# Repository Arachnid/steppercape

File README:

Schematics and firmware for the Beaglebone stepper cape.

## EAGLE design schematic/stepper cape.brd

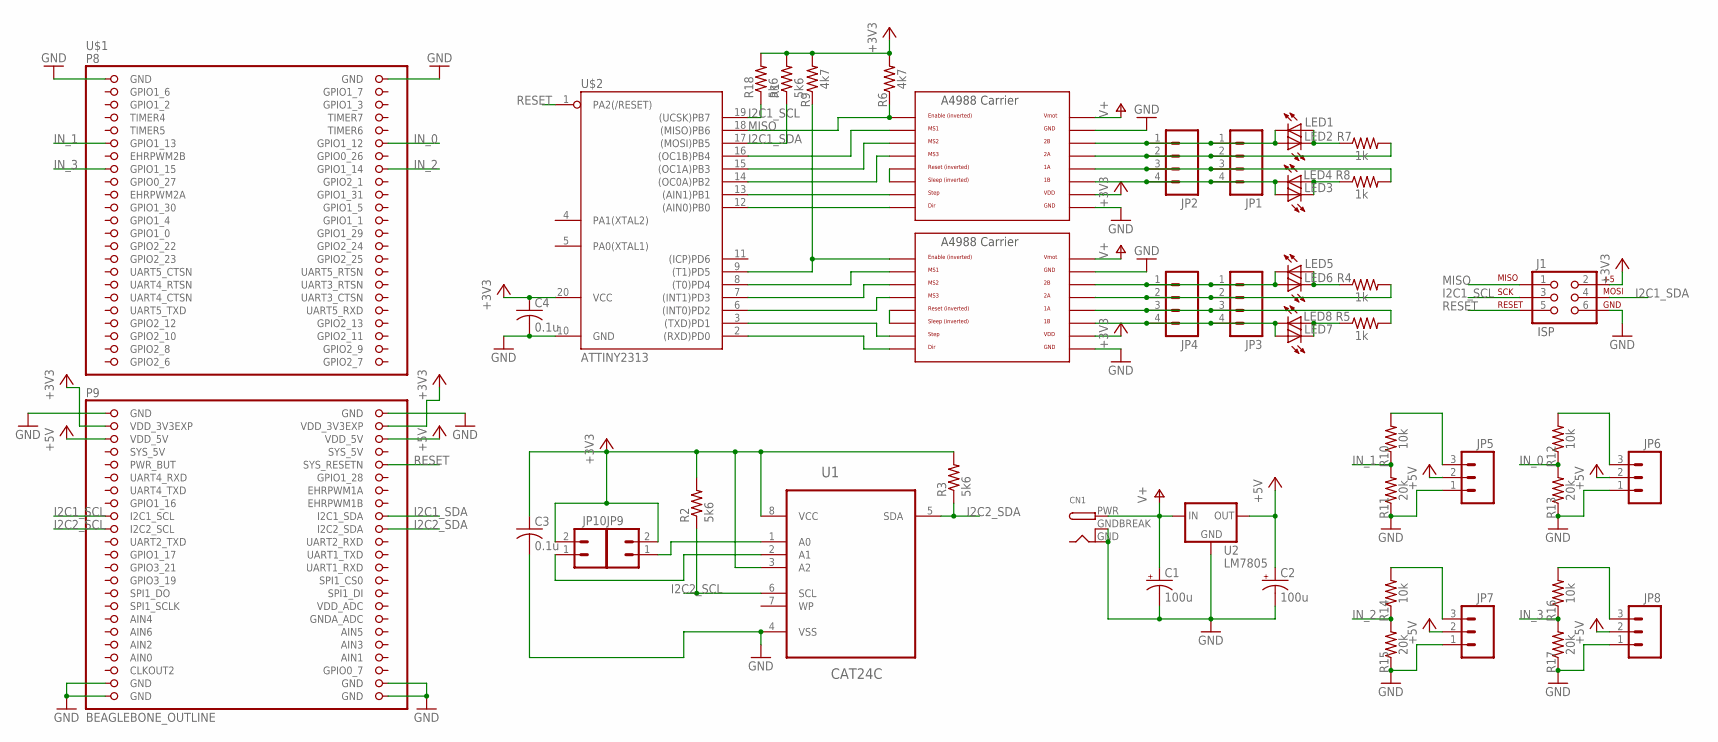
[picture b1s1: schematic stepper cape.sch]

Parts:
C1, C2: 100u; E2,5-6
C3, C4: 0.1u; C1206
CN1: DCBARRELPTH; DCJACK_2MM_PTH
J1: ISP; 2X3
JP1, JP3: M04SCREW; SCREWTERMINAL-3.5MM-4
JP2, JP4: M04PTH; 1X04
JP5, JP6, JP7, JP8: M03PTH; 1X03
JP9, JP10: M02PTH; 1X02
LED1, LED2, LED3, LED4, LED5, LED6, LED7, LED8: LEDCHIPLED_1206; CHIPLED_1206
R1, R2, R3, R18: 5k6; R1206
R4, R5, R7, R8: 1k; R1206
R6, R9: 4k7; R1206
R10, R12, R14, R16: 10k; R1206
R11, R13, R15, R17: 20k; R1206
U1: CAT24C; SOIC127P600X175-8N
U2: LM7805; TO220-IGO
U$1: BEAGLEBONE_OUTLINE; BEAGLEBONE_SHIELD
U$2: ATTINY2313; SO20L$
X, X1: A4988BREAKOUT

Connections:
+3V3: C3.1, C4.1, J1.2, JP9.2, JP10.2, R1.2, R2.2, R3.2, R6.2, R9.2, R18.2, U1.3 (A2), U1.8 (VCC), U$1.49 (VDD_3V3EXP), U$1.50 (VDD_3V3EXP), U$2.20 (VCC), X.VDD, X1.VDD
+5V: C2.+, JP5.2, JP6.2, JP7.2, JP8.2, U2.OUT, U$1.51 (VDD_5V), U$1.52 (VDD_5V)
AIN0: U$1.85 (AIN0)
AIN3: U$1.84 (AIN3)
GND: C1.-, C2.-, C3.2, C4.2, CN1.GND, CN1.GNDBREAK, J1.6, JP5.1, JP6.1, JP7.1, JP8.1, R11.1, R13.1, R15.1, R17.1, U1.4 (VSS), U2.GND, U$1.1 (GND), U$1.2 (GND), U$1.47 (GND), U$1.48 (GND), U$1.89 (GND), U$1.90 (GND), U$1.91 (GND), U$1.92 (GND), U$2.10 (GND), X.GND, X.GND@0 (GND), X1.GND, X1.GND@0 (GND)
GPIO1_6: U$1.3 (GPIO1_6)
GPIO1_7: U$1.4 (GPIO1_7)
GPIO2_6: U$1.45 (GPIO2_6)
GPIO2_7: U$1.46 (GPIO2_7)
GPIO2_8: U$1.43 (GPIO2_8)
GPIO2_9: U$1.44 (GPIO2_9)
GPIO2_11: U$1.42 (GPIO2_11)
I2C1_SCL: J1.3, R18.1, U$1.63 (I2C1_SCL), U$2.19 ((UCSK)PB7)
I2C1_SDA: J1.4, R1.1, U$1.64 (I2C1_SDA), U$2.17 ((MOSI)PB5)
I2C2_SCL: R2.1, U1.6 (SCL), U$1.65 (I2C2_SCL)
I2C2_SDA: R3.1, U1.5 (SDA), U$1.66 (I2C2_SDA)
IN_0: R12.1, R13.2, U$1.12 (GPIO1_12)
IN_1: R10.1, R11.2, U$1.11 (GPIO1_13)
IN_2: R14.1, R15.2, U$1.16 (GPIO1_14)
IN_3: R16.1, R17.2, U$1.15 (GPIO1_15)
MISO: J1.1, R6.1, U$2.18 ((MISO)PB6), X.EN
unnamed: JP9.1, U1.1 (A0)
unnamed: U$2.2 ((RXD)PD0), X1.DIR
unnamed: JP10.1, U1.2 (A1)
unnamed: U$2.3 ((TXD)PD1), X1.STEP
unnamed: JP1.1, JP2.1, LED1.C, LED2.A, X.2B
unnamed: U$2.6 ((INT0)PD2), X1.MS3
unnamed: U$2.7 ((INT1)PD3), X1.MS2
unnamed: U$2.8 ((T0)PD4), X1.MS1
unnamed: X1.RST, X1.SLP (SLEEP)
unnamed: JP3.1, JP4.1, LED5.C, LED6.A, X1.2B
unnamed: JP3.2, JP4.2, R4.2, X1.2A
unnamed: X.RST, X.SLP (SLEEP)
unnamed: JP1.2, JP2.2, R7.2, X.2A
unnamed: JP1.3, JP2.3, R8.2, X.1A
unnamed: JP1.4, JP2.4, LED3.A, LED4.C, X.1B
unnamed: LED1.A, LED2.C, R7.1
unnamed: JP3.3, JP4.3, R5.2, X1.1A
unnamed: LED3.C, LED4.A, R8.1
unnamed: JP3.4, JP4.4, LED7.A, LED8.C, X1.1B
unnamed: LED5.A, LED6.C, R4.1
unnamed: LED7.C, LED8.A, R5.1
unnamed: R9.1, U$2.9 ((T1)PD5), X1.EN
unnamed: U$2.12 ((AIN0)PB0), X.DIR
unnamed: U$2.13 ((AIN1)PB1), X.STEP
unnamed: JP6.3, R12.2
unnamed: JP5.3, R10.2
unnamed: JP7.3, R14.2
unnamed: JP8.3, R16.2
unnamed: U$2.14 ((OC0A)PB2), X.MS3
unnamed: U$2.15 ((OC1A)PB3), X.MS2
unnamed: U$2.16 ((OC1B)PB4), X.MS1
RESET: J1.5, U$1.56 (SYS_RESETN), U$2.1 (PA2(/RESET))
V+: C1.+, CN1.PWR, U2.IN, X.VMOT, X1.VMOT

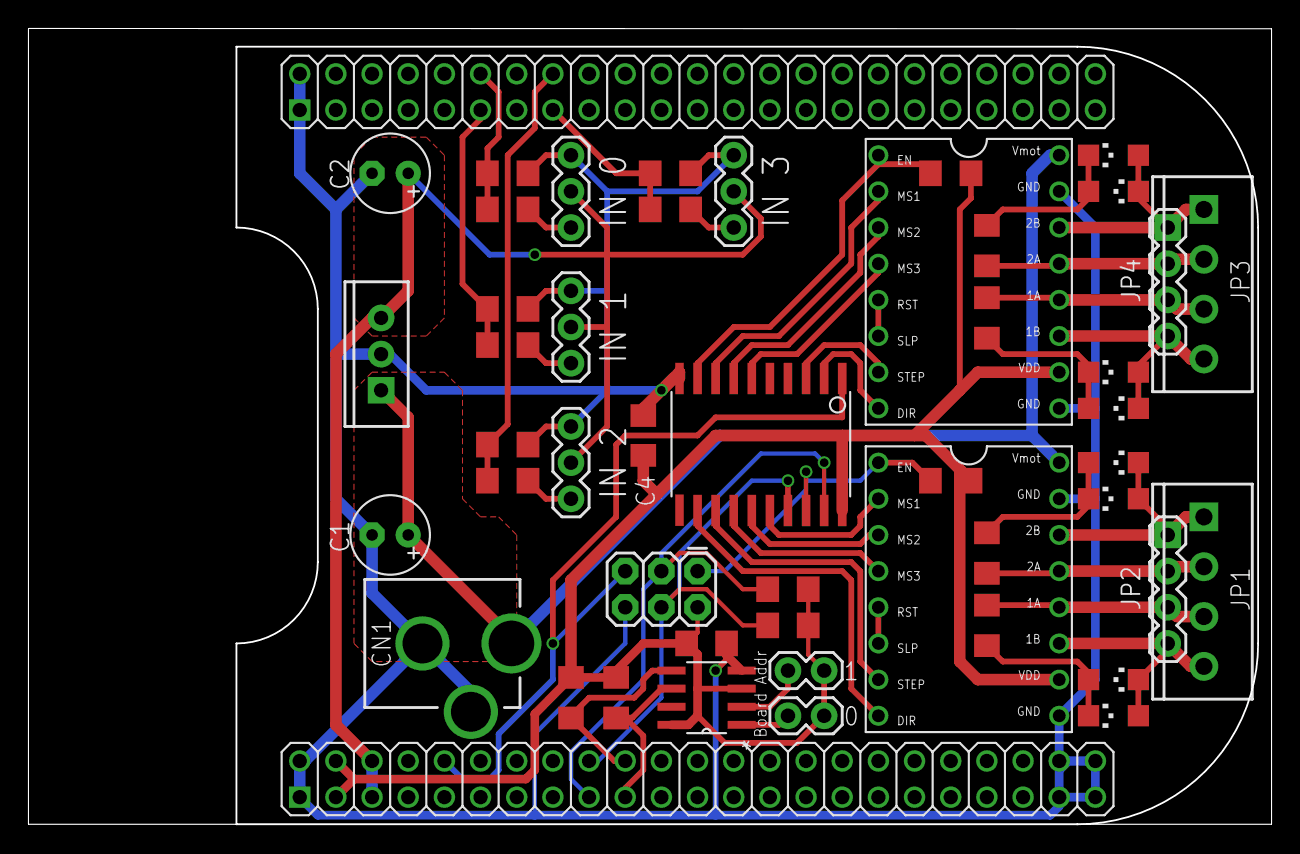
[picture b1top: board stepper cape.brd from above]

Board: 2 copper layers, 87.2 x 55.8 mm, 49 parts (1 on the bottom side), 45 nets.

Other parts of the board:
U$3: OSHW_FILLX500_NOTEXT

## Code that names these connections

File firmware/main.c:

/*
 * Stepper Cape - an I2C based stepper driver cape for the Beaglebone
 * Copyright (C) 2012 Nick Johnson
 *
 * This program is free software; you can redistribute it and/or
 * modify it under the terms of the GNU General Public License
 * as published by the Free Software Foundation; either version 2
 * of the License, or (at your option) any later version.
 * 
 * This program is distributed in the hope that it will be useful,
 * but WITHOUT ANY WARRANTY; without even the implied warranty of
 * MERCHANTABILITY or FITNESS FOR A PARTICULAR PURPOSE.  See the
 * GNU General Public License for more details.
 * 
 * You should have received a copy of the GNU General Public License
 * along with this program; if not, write to the Free Software
 * Foundation, Inc., 51 Franklin Street, Fifth Floor, Boston, MA  02110-1301, USA.
 */

#define F_CPU 8000000UL  // 8 MHz

#include <util/delay.h>
#include <avr/io.h>
#include <avr/eeprom.h>
#include <avr/interrupt.h>
#include <avr/pgmspace.h>
#include "register.h"
#include "usiTwiSlave.h"

FUSES = {
	.low = FUSE_SUT0 & FUSE_CKSEL3 & FUSE_CKSEL1 & FUSE_CKSEL0,
	.high = FUSE_SPIEN,
};

#define TRUE 1
#define FALSE 0

#define DDR_STEPPER0 DDRB
#define PORT_STEPPER0 PORTB
#define STEPPER0_DIR PB0
#define STEPPER0_EN PB6
#define STEPPER0_STEP PB1
#define STEPPER0_MS0 PB2
#define STEPPER0_MICROSTEP_MASK ((uint8_t)~(_BV(PB4) | _BV(PB3) | _BV(PB2)))

#define DDR_STEPPER1 DDRD
#define PORT_STEPPER1 PORTD
#define STEPPER1_DIR PD0
#define STEPPER1_EN PD5
#define STEPPER1_STEP PD1
#define STEPPER1_MS0 PD2
#define STEPPER1_MICROSTEP_MASK ((uint8_t)~(_BV(PD4) | _BV(PD3) | _BV(PD2)))

#define PORT_INPUTS PORTA
#define INPUT0 PA0
#define INPUT1 PA1

#define ENABLE_PWM_SETUP() (TCCR1A = 0, TCCR1B = _BV(WGM13) | _BV(WGM12), TIMSK |= _BV(ICIE1))

typedef uint8_t (*register_write_handler)(uint8_t reg, uint8_t oldval);

// Predefinitions of read/write handlers so we can reference them
uint8_t i2c_read(uint8_t reg, volatile uint8_t *value);
uint8_t i2c_write(uint8_t reg, uint8_t value);
void main(void) __attribute__((noreturn));

#define copy_bit(from_reg, from_bit, to_reg, to_bit) if((from_reg) & _BV(from_bit)) { \
    to_reg |= _BV(to_bit); \
} else { \
    to_reg &= ~_BV(to_bit); \
}

register_t registers;

#define BUFFER_CAPACITY 32
volatile uint8_t buffer[BUFFER_CAPACITY];
volatile uint8_t buffer_head = 0; // Oldest valid element
volatile uint8_t buffer_tail = 0; // First empty slot
volatile uint8_t buffer_nybble = 0;

// EEPROM copy of registers; updated on write to register 127.
register_t EEMEM eeprom_registers = {
    .reg = {
        .slave_addr = 0x26,
        .clk_flags = {
			.stall_stop = 0,
			.cs = 0,
		},
        .step_interval = 0,
        .limit_flags = {
			.s0_stop = 0,
			.s1_stop = 0,
			.i0_invert = 0,
			.i1_invert = 0,
		},
        .microstep = {
			.stepper0 = 0,
			.stepper1 = 0,
		},
        .buffer_free = BUFFER_CAPACITY,
        .buffer_append = 0
    }
};

volatile uint8_t eeprom_dirty = FALSE;

uint8_t write_noop(uint8_t reg, uint8_t oldval) {
	return TRUE;
}

uint8_t write_ignore(uint8_t reg, uint8_t oldval) {
	registers.bytes[reg] = oldval;
	return TRUE;
}

uint8_t write_slave_addr(uint8_t reg, uint8_t oldval) {
    usiTwiSlaveInit(registers.reg.slave_addr, i2c_read, i2c_write);
	return TRUE;
}

uint8_t write_clk_flags(uint8_t reg, uint8_t oldval) {
	// Copy lower 3 bits to clock select flags
	TCCR1B = (TCCR1B & 0xF8) | registers.reg.clk_flags.cs;
	return TRUE;
}

uint8_t write_step_interval_msb(uint8_t reg, uint8_t oldval) {
	// Update counter max value
	ICR1 = registers.reg.step_interval;
	return TRUE;
}

uint8_t write_limit_flags(uint8_t reg, uint8_t oldval) {
	if(registers.reg.limit_flags.i0_pullup) {
		PORT_INPUTS |= _BV(INPUT0);
	} else {
		PORT_INPUTS &= ~_BV(INPUT0);
	}
	if(registers.reg.limit_flags.i1_pullup) {
		PORT_INPUTS |= _BV(INPUT1);
	} else {
		PORT_INPUTS &= ~_BV(INPUT1);
	}
	return TRUE;
}

uint8_t write_microstep(uint8_t reg, uint8_t oldval) {
	// Update output pins with respective microstep settings
	PORT_STEPPER0 = (PORT_STEPPER0 & STEPPER0_MICROSTEP_MASK) | registers.reg.microstep.stepper0 << STEPPER0_MS0;
	PORT_STEPPER1 = (PORT_STEPPER1 & STEPPER1_MICROSTEP_MASK) | registers.reg.microstep.stepper1 << STEPPER0_MS0;
	return TRUE;
}

uint8_t buffer_append(uint8_t reg, uint8_t oldval) {
	buffer[buffer_tail] = registers.reg.buffer_append;
	registers.reg.buffer_append = 0;
	buffer_tail = (buffer_tail + 1) % BUFFER_CAPACITY;
	registers.reg.buffer_free -= 1;
	// Only ack if the buffer is not full
	return registers.reg.buffer_free;
}

// 00 = disable
// 01 = stop
// 10 = step back
// 11 = step forward

ISR(TIMER1_CAPT_vect) {
	// Step pins low
	PORT_STEPPER0 &= ~_BV(STEPPER0_STEP);
	PORT_STEPPER1 &= ~_BV(STEPPER1_STEP);

	if(registers.reg.buffer_free < BUFFER_CAPACITY) {
		// Fetch current instruction
		uint8_t data = (buffer[buffer_head] >> (buffer_nybble << 2)) & 0xF;
		buffer_head = (buffer_head + buffer_nybble) % BUFFER_CAPACITY;

		// If we're about to make the buffer non-full, ack the pending write
		if(registers.reg.buffer_free == 0 && buffer_nybble)
			usiTwiSlaveAck();

		registers.reg.buffer_free += buffer_nybble;
		buffer_nybble ^= 1;
		
		uint8_t in0 = ((PORT_INPUTS & _BV(INPUT0)) != 0) ^ registers.reg.limit_flags.i0_invert;
		uint8_t in1 = ((PORT_INPUTS & _BV(INPUT1)) != 0) ^ registers.reg.limit_flags.i1_invert;
		if(!in0 || !registers.reg.limit_flags.s0_stop) {
			if(data & 0x2) {
				// Step instruction
				copy_bit(data, 0, PORT_STEPPER0, STEPPER0_DIR);
				PORT_STEPPER0 &= ~_BV(STEPPER0_EN);
				PORT_STEPPER0 |= _BV(STEPPER0_STEP);
			} else {
				// Stop or disable instruction
				copy_bit(~data, 0, PORT_STEPPER0, STEPPER0_EN);
			}
		}

		if(!in1 || !registers.reg.limit_flags.s1_stop) {
			if(data & 0x8) {
				// Step instruction
				copy_bit(data, 2, PORT_STEPPER1, STEPPER1_DIR);
				PORT_STEPPER1 &= ~_BV(STEPPER1_EN);
				PORT_STEPPER1 |= _BV(STEPPER1_STEP) | _BV(STEPPER1_EN);
			} else {
				// Stop or disable instruction
				copy_bit(~data, 2, PORT_STEPPER1, STEPPER1_EN);
			}
		}
	} else {
		// Buffer underrun! Stall!
		if(registers.reg.clk_flags.stall_stop) {
			// Stop the timer when the buffer is empty
			registers.reg.clk_flags.cs = 0;
			TCCR1B &= 0xF8;
			
			PORT_STEPPER0 |= _BV(STEPPER0_EN);
			PORT_STEPPER1 |= _BV(STEPPER1_EN);
		}
	}
}

const register_write_handler write_handlers[] = {
    write_slave_addr,
    write_clk_flags,
    write_noop,
    write_step_interval_msb,
    write_limit_flags,
    write_microstep,
    write_ignore,
    buffer_append,
};

uint8_t i2c_read(uint8_t reg, volatile uint8_t *value) {
    if(reg < NUM_REGISTERS) {
        *value = registers.bytes[reg];
    } else {
		*value = 0;
    }
    // Send ACK
    return TRUE;
}

uint8_t i2c_write(uint8_t reg, uint8_t value) {
	uint8_t ret = 1;
    if(reg < NUM_REGISTERS) {
//		ret = ((register_write_handler)pgm_read_word_near(write_handlers + reg))(reg, &value);
		uint8_t oldval = registers.bytes[reg];
		registers.bytes[reg] = value;
        ret = write_handlers[reg](reg, oldval);
    } else if(reg == 127) {
        // Update eeprom (asynchronously, so we don't block the interrupt).
        eeprom_dirty = TRUE;
    } else {
        // Invalid register - do nothing.
    }
    return ret;
}

void ioinit(void) {
	// Set all the output pins
    DDR_STEPPER0 |= _BV(STEPPER0_DIR) | _BV(STEPPER0_EN) |
                    _BV(STEPPER0_STEP) | _BV(STEPPER0_MS0) |
                    _BV(STEPPER0_MS0 + 1) | _BV(STEPPER0_MS0 + 2);
    DDR_STEPPER1 |= _BV(STEPPER1_DIR) | _BV(STEPPER1_EN) |
                    _BV(STEPPER1_STEP) | _BV(STEPPER1_MS0) |
                    _BV(STEPPER1_MS0 + 1) | _BV(STEPPER1_MS0 + 2);
                    
    // Set enable pins to 1, since they're active-low
    PORT_STEPPER0 |= _BV(STEPPER0_EN);
    PORT_STEPPER1 |= _BV(STEPPER1_EN);
    
    // Setup PWM: Clear timer on compare. Don't enable it yet.
    ENABLE_PWM_SETUP();
}

void read_registers(void) {
    // Initialize from eeprom
    eeprom_read_block(&registers, &eeprom_registers, sizeof(registers) - 1);

    // Run all the write funcs in order to initialize the device
    // But don't write to the buffer append register!
    for(int i = 0; i < NUM_REGISTERS - 1; i++)
        write_handlers[i](i, registers.bytes[i]);

	registers.reg.buffer_free = BUFFER_CAPACITY;
}

void main(void) {
    ioinit();
    read_registers();
    // Enable interrupts
    sei();
    
    for(;;) {
        if(eeprom_dirty) {
            eeprom_write_block(&registers, &eeprom_registers, sizeof(registers));
            eeprom_dirty = FALSE;
        }
    }
}

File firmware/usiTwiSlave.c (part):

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#  define DDR_USI             DDRB
#  define PORT_USI            PORTB
#  define PIN_USI             PINB
#  define PORT_USI_SDA        PB5
#  define PORT_USI_SCL        PB7
#  define PIN_USI_SDA         PINB5
#  define PIN_USI_SCL         PINB7
#  define USI_START_COND_INT  USISIF
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#  define DDR_USI             DDRB
#  define PORT_USI            PORTB
#  define PIN_USI             PINB
#  define PORT_USI_SDA        PB0
#  define PORT_USI_SCL        PB2
#  define PIN_USI_SDA         PINB0
#  define PIN_USI_SCL         PINB2
#  define USI_START_COND_INT  USISIF
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#  define DDR_USI             DDRB
#  define PORT_USI            PORTB
#  define PIN_USI             PINB
#  define PORT_USI_SDA        PB0
#  define PORT_USI_SCL        PB2
#  define PIN_USI_SDA         PINB0
#  define PIN_USI_SCL         PINB2
#  define USI_START_COND_INT  USISIF
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#  define DDR_USI             DDRB
#  define PORT_USI            PORTB
#  define PIN_USI             PINB
#  define PORT_USI_SDA        PB0
#  define PORT_USI_SCL        PB2
#  define PIN_USI_SDA         PINB0
#  define PIN_USI_SCL         PINB2
#  define USI_START_COND_INT  USISIF
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
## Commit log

2012-05-23 Connected spare IO pins on AVR to inputs 0 and 1; changed to 0805 parts instead of 1206.
2012-05-28 First version of firmware
2012-05-28 Added limit switch support
2012-05-28 Broke more flags registers out into bitfields; added pullup support for inputs
2012-05-28 Removed names for padding fields
2012-05-28 More flags registers to bitfields; converted write functions to be executed after value set, instead of before
2012-05-28 Fixed timer interrupt, clock stretching, and microstep select

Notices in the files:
parts and their libraries:
SparkFun-Connectors: Licensing: CC v3.0 Share-Alike You are welcome to use this library for commercial purposes.
